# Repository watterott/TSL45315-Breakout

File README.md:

# TSL45315-Breakout
Breakout with AMS TSL4531 Digital Ambient Light Sensor.

* [AMS TSL4531](https://ams.com/TSL45313) Light Sensor
* Direct lux output with wide dynamic range
* Range: 3 lux to 220k lux
* Rejects 50Hz/60Hz lighting ripple
* Approximates human eye response in diverse lighting conditions
* TWI/I2C Interface (address 0x29=TSL45315, 0x39=TSL45311)
* 3.3V - 5V Power Supply and Logic Level
* Open-Source and released under the [Creative Commons Attribution Share-Alike License](https://creativecommons.org/licenses/by-sa/4.0/).
* **[Documentation on learn.watterott.com](https://learn.watterott.com)**

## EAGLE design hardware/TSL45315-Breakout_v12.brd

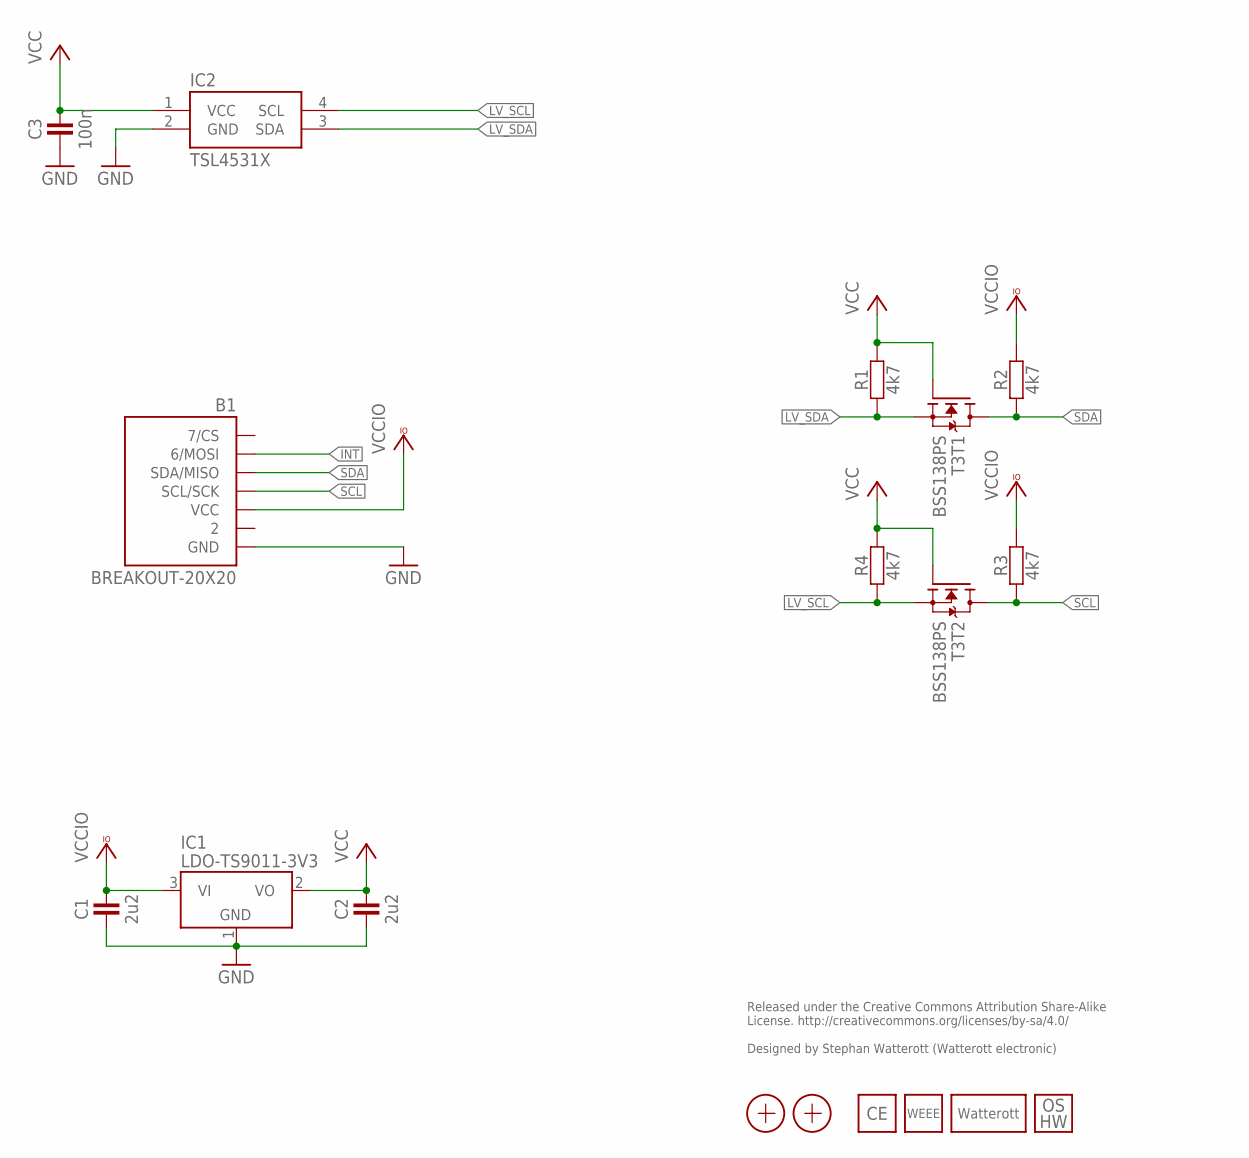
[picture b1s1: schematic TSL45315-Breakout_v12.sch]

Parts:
B1: BREAKOUT-20X20
C1, C2: 2u2; C0402
C3: 100n; C0402
IC1: LDO-TS9011-3V3; SOT23
IC2: TSL4531X; AMS_CL
LOGO3: LOGO_WEEE-4; WEEE_4MM
LOGO4: LOGO_CE-4; CE_4MM
LOGO5: LOGO_SPARK-4; SPARK_4MM
LOGO6: LOGO_OSHW-2; OSHW_2MM
R1, R2, R3, R4: 4k7; C0402
T3: BSS138PS; SOT363
X1, X2: PASSER-07; PASSER_07MM

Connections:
GND: B1.GND, C1.1, C2.1, C3.1, IC1.1 (GND), IC2.2 (GND)
INT: B1.MOSI (6/MOSI)
LV_SCL: IC2.4 (SCL), R4.1, T3.4 (S)
LV_SDA: IC2.3 (SDA), R1.1, T3.1 (S)
SCL: B1.SCL/SCK, R3.1, T3.3 (D)
SDA: B1.SDA/MISO, R2.1, T3.6 (D)
VCC: C2.2, C3.2, IC1.2 (VO), IC2.1 (VCC), R1.2, R4.2, T3.2 (G), T3.5 (G)
VCCIO: B1.VCC, C1.2, IC1.3 (VI), R2.2, R3.2

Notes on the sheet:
Released under the Creative Commons Attribution Share-Alike License. http://creativecommons.org/licenses/by-sa/4.0/ Designed by Stephan Watterott (Watterott electronic)

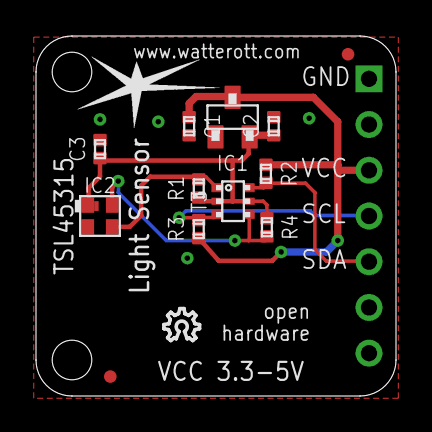
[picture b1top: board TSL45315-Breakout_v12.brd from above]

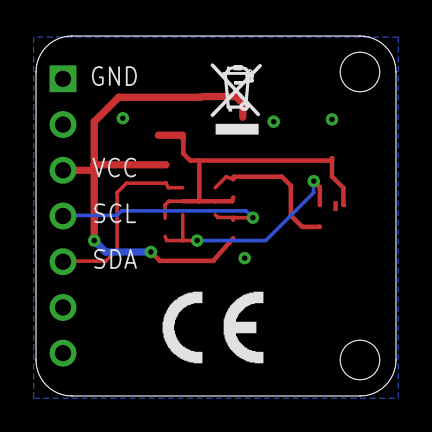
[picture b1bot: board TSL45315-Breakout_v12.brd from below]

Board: 2 copper layers, 20.0 x 20.0 mm, 17 parts (2 on the bottom side), 7 nets.

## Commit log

2019-11-03 added rev 1.2
2020-05-16 updated example
2020-06-03 No need to clear the buffer after a Wire.requestFrom.
    Explanation: https://github.com/Koepel/How-to-use-the-Arduino-Wire-library/wiki/Common-mistakes#4
    Beside that, when the Master call Wire.requestFrom to requests 2 bytes, then it is impossible that it will have more than two bytes.
